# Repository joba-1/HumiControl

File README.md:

# Humidity Control

## Current Status

* A Bosch BME280 delivers air humidity data
* An analog capacitive moisture sensor delivers soil humidity data
* A fan is controlled with a pwm pin via web slider control or flash button
* Automatic mode uses humidity value to set fan speed.
* Setup wifi with captive portal.
* Reset wifi settings with long press of flash button
* Led feedback:
    * fast blink: boot setup and wifi connect
    * slow blink: wifi setup
    * on: normal operation
    * off: flash button pressed (on again if long press detected)

## Todo

* mDNS does not work properly
* mqtt integration
* configurable limits for the automatic fan control

## Flash Software Installation

Precondition: Python V2

### PlatformIO

    pip install platformio

### Arduino Framework for PlatformIO

    pio platforms install espressif8266 --with-package framework-arduinoespressif8266

## Wiring

If you want to use other pins, adjust the #defines accordingly.

### BME280

This is a breadboard friendly wiring for a standard BME280 breakout board and a NodeMCU:
All pins align, no extra wiring necessary.

    BME280 GND <--> ESP8266 GND
    BME280 SCL <--> ESP8266 D5 (D1 is standard)
    BME280 SDA <--> ESP8266 D6 (D2 is standard)
    BME280 3V3 <--> ESP8266 3V3

### Capacitive Soil Moisture Sensor (V1.2)

    CAP GND  <--> ESP8266 GND
    CAP VCC  <--> ESP8266 3V3
    CAP AOUT <--> ESP8266 A0

### Fan Power

    for PWM control of a fan connect D5 with mosfet gate.
    Schematics and pcb board are in the eagle/ subfolder (warning: uses rare p-channel mosfet).

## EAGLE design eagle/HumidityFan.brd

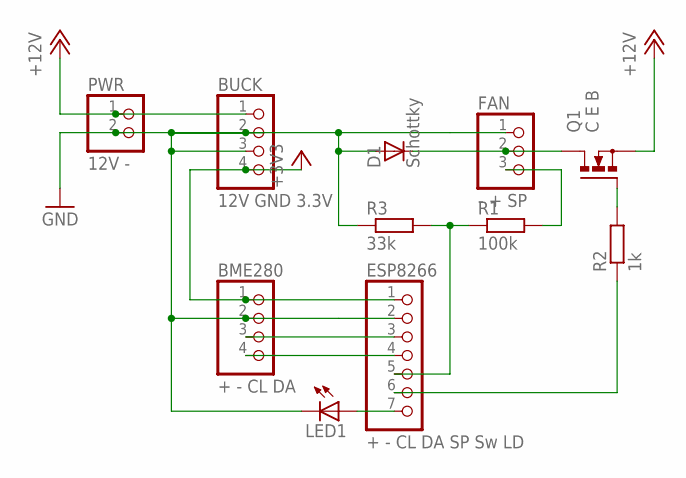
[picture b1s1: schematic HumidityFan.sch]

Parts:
BME280: + - CL DA; 1X04
BUCK: 12V GND 3.3V; 1X04
D1: Schottky; DO35-10
ESP8266: + - CL DA SP Sw LD; 1X07
FAN: - + SP; 1X03
LED1: LED5MM
PWR: 12V -; 1X02
Q1: C E B; TO220BV
R1: 100k; 0204/7
R2: 1k; 0204/7
R3: 33k; 0204/7

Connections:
+3V3: BME280.1, BUCK.4, ESP8266.1
+12V: BUCK.1, PWR.1, Q1.S
GND: BME280.2, BUCK.2, BUCK.3, D1.A, ESP8266.2, FAN.1, LED1.K (C), PWR.2, R3.1
unnamed: Q1.G, R2.2
unnamed: D1.C, FAN.2, Q1.D
unnamed: ESP8266.6, R2.1
unnamed: ESP8266.7, LED1.A
SCL: BME280.3, ESP8266.3
SDA: BME280.4, ESP8266.4
SPD3.3V: ESP8266.5, R1.1, R3.2
SPD12V: FAN.3, R1.2

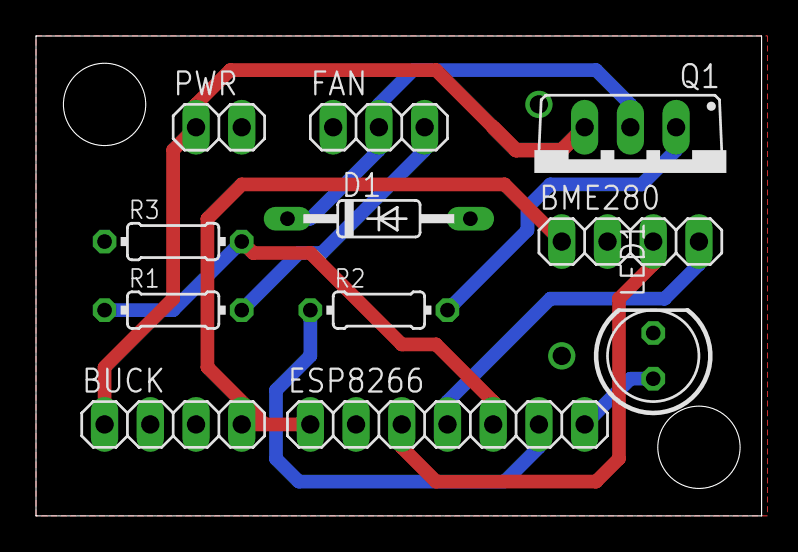
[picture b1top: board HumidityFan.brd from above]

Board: 2 copper layers, 40.3 x 26.7 mm, 11 parts (0 on the bottom side), 11 nets.

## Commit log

2019-03-03 Humidity Control - measure humidity and control a fan
2019-03-03 added bme280 lib, switched to OTA
2019-03-03 Fix problem with name resolution
2019-03-04 Use other pins to better line up with the connector. Use external LED for feedback. Fan control with web page buttons and physical (flash) button short press (long press is still wlan config reset)
2019-03-04 add fan speed control
2019-03-05 increase msg buffer
2019-03-05 better pwm fan speed handling
2019-03-05 fix setting speed and add uptime
2019-03-05 Setting hostname breaks WlanManager
2019-03-05 include uptime in json response
2019-03-05 dont quote uptime
2019-03-05 validate soil moisture
2019-03-06 add eagle pcb
2019-03-06 switch fan on and off button
2019-03-06 fix json NaN ignorance
2019-03-06 add domoticz lua parser for this sensor
2019-03-10 automatic humidity driven fan speed
2019-03-10 add auto flag to json status
2019-03-10 persistent setting for automatic fan speed flag (default is off)
2019-03-10 button press toggles fan off -> on -> auto -> off
2019-03-10 update speed after toggle to automatic fan control
2019-03-10 Update Design.md
    md formatting
